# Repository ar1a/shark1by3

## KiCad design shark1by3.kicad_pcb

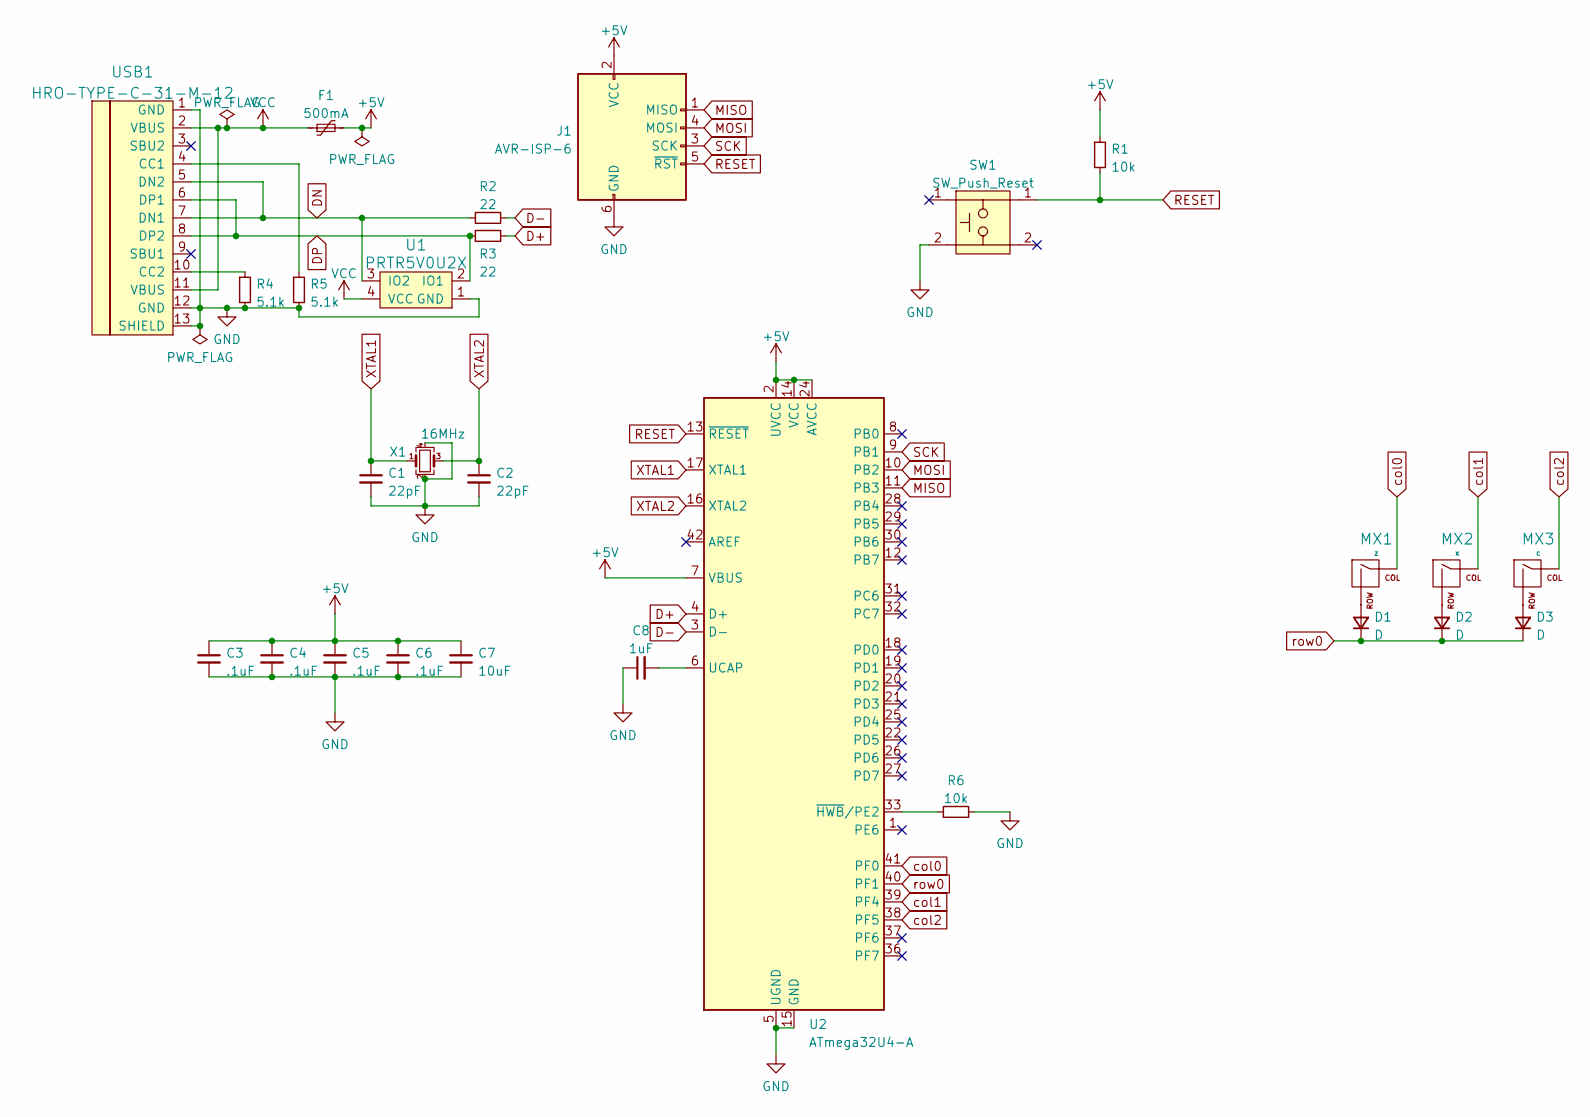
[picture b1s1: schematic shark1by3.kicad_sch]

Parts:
C1, C2: 22pF; C_0805_2012Metric_Pad1.18x1.45mm_HandSolder
C3, C4, C5, C6: .1uF; C_0805_2012Metric_Pad1.18x1.45mm_HandSolder
C7: 10uF; C_0805_2012Metric_Pad1.18x1.45mm_HandSolder
C8: 1uF; C_0805_2012Metric_Pad1.18x1.45mm_HandSolder
D1, D2, D3: D; D_SOD-123
F1: 500mA; Fuse_1206_3216Metric_Pad1.42x1.75mm_HandSolder
J1: AVR-ISP-6; Reset_Pretty-Mask
MX1: Z; MXOnly-1U-Hotswap-Antishear
MX2: X; MXOnly-1U-Hotswap-Antishear
MX3: C; MXOnly-1U-Hotswap-Antishear
R1, R6: 10k; R_0805_2012Metric_Pad1.20x1.40mm_HandSolder
R2, R3: 22; R_0805_2012Metric_Pad1.20x1.40mm_HandSolder
R4, R5: 5.1k; R_0805_2012Metric_Pad1.20x1.40mm_HandSolder
SW1: SW_Push_Reset; SW_SPST_SKQG_WithStem
U1: PRTR5V0U2X; SOT143B
U2: ATmega32U4-A; TQFP-44_10x10mm_P0.8mm
USB1: HRO-TYPE-C-31-M-12; HRO-TYPE-C-31-M-12-HandSoldering
X1: 16MHz; Crystal_SMD_3225-4Pin_3.2x2.5mm_HandSoldering

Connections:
+5V: C3.1, C4.1, C5.1, C6.1, C7.1, F1.2, J1.2 (VCC), R1.1, U2.2 (UVCC), U2.7 (VBUS), U2.14 (VCC), U2.24 (AVCC), U2.34 (VCC), U2.44 (AVCC)
D+: R3.2, U2.4 (D+)
D-: R2.2, U2.3 (D-)
DN: R2.1, U1.3 (IO2), USB1.5 (DN2), USB1.7 (DN1)
DP: R3.1, U1.2 (IO1), USB1.6 (DP1), USB1.8 (DP2)
GND: C1.2, C2.2, C3.2, C4.2, C5.2, C6.2, C7.2, C8.1, J1.6 (GND), R4.2, R5.2, R6.2, SW1.2, U1.1 (GND), U2.5 (UGND), U2.15 (GND), U2.23 (GND), U2.35 (GND), U2.43 (GND), USB1.1 (GND), USB1.12 (GND), USB1.13 (SHIELD), X1.2, X1.4
MISO: J1.1 (MISO), U2.11 (PB3)
MOSI: J1.4 (MOSI), U2.10 (PB2)
unnamed: C8.2, U2.6 (UCAP)
unnamed: D1.2 (A), MX1.2 (ROW)
unnamed: D2.2 (A), MX2.2 (ROW)
unnamed: D3.2 (A), MX3.2 (ROW)
unnamed: R4.1, USB1.10 (CC2)
unnamed: R5.1, USB1.4 (CC1)
unnamed: R6.1, U2.33 (~HWB/PE2)
RESET: J1.5 (~RST), R1.2, SW1.1, U2.13 (~RESET)
SCK: J1.3 (SCK), U2.9 (PB1)
VCC: F1.1, U1.4 (VCC), USB1.2 (VBUS), USB1.11 (VBUS)
XTAL1: C1.1, U2.17 (XTAL1), X1.1
XTAL2: C2.1, U2.16 (XTAL2), X1.3
col0: MX1.1 (COL), U2.41 (PF0)
col1: MX2.1 (COL), U2.39 (PF4)
col2: MX3.1 (COL), U2.38 (PF5)
row0: D1.1 (K), D2.1 (K), D3.1 (K), U2.40 (PF1)

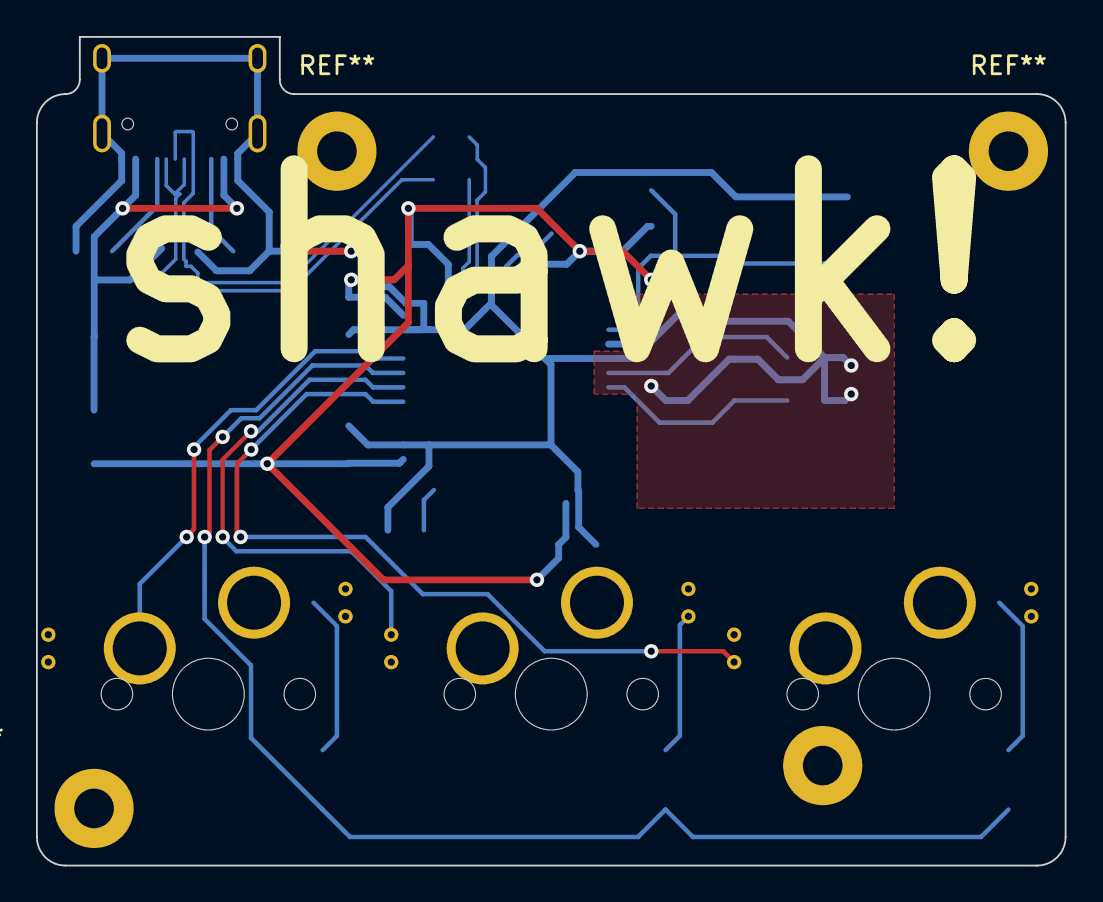
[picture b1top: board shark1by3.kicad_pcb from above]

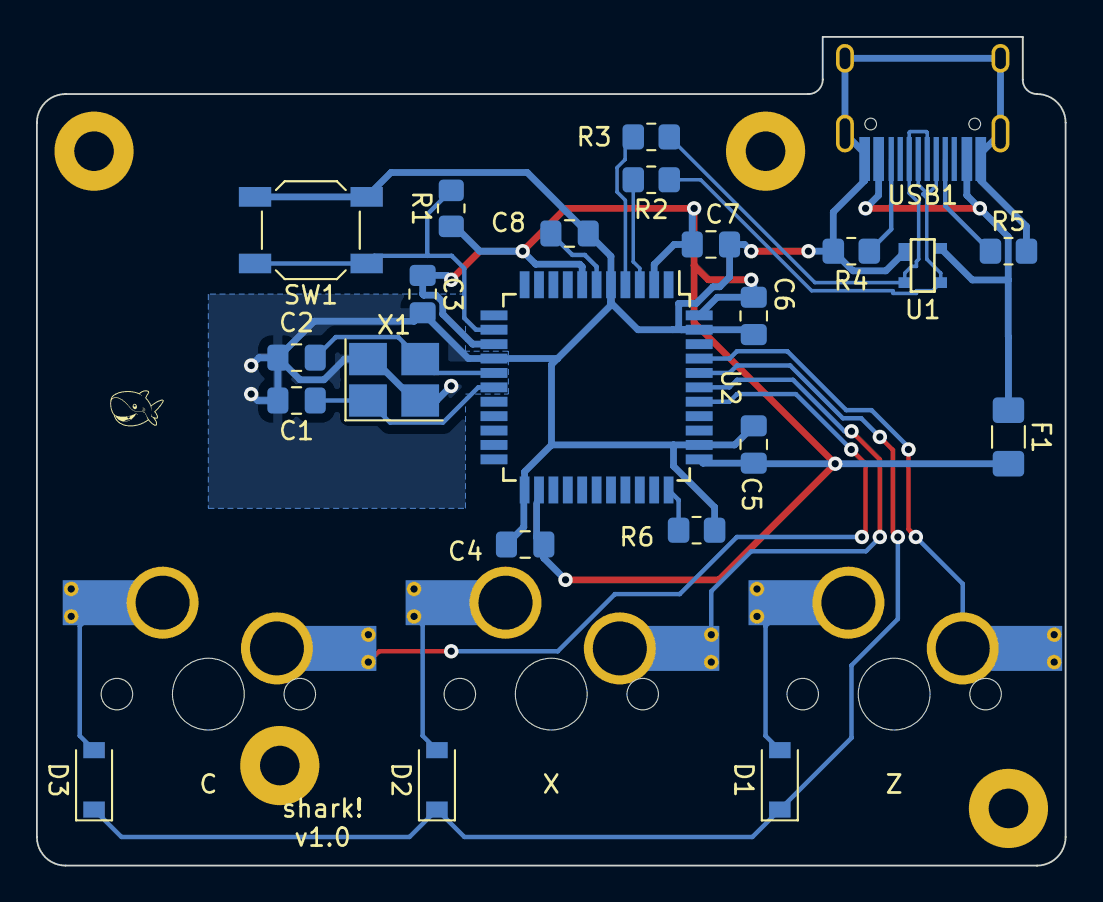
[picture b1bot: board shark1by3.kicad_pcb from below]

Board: 2 copper layers, 57.2 x 46.0 mm, 26 parts (23 on the bottom side), 21 nets.

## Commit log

2022-05-22 init
2022-05-22 plan schema
2022-05-22 route pcb
2022-05-22 antishear bois
2022-05-22 add silk screen stuff
2022-05-22 tweak some ground pads
2022-05-22 add rendered pngs
2022-05-23 shorten data lines
2022-05-23 add scuffed mounting holes
